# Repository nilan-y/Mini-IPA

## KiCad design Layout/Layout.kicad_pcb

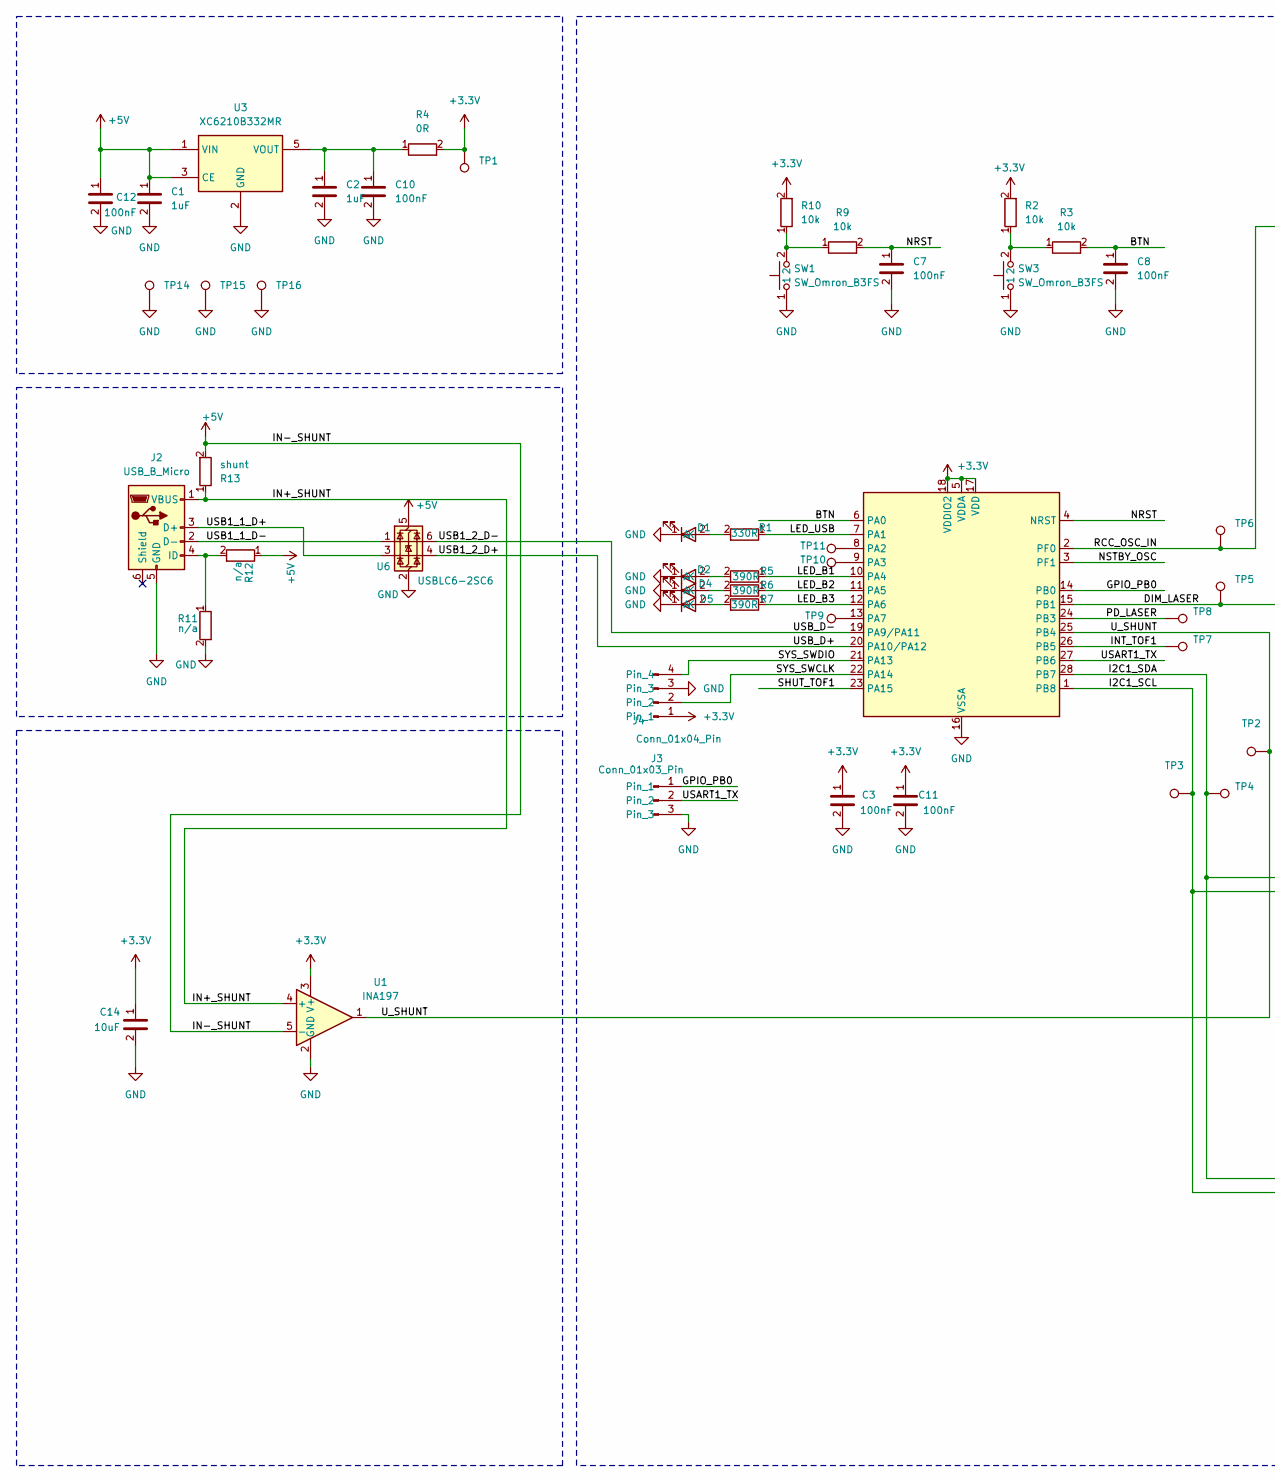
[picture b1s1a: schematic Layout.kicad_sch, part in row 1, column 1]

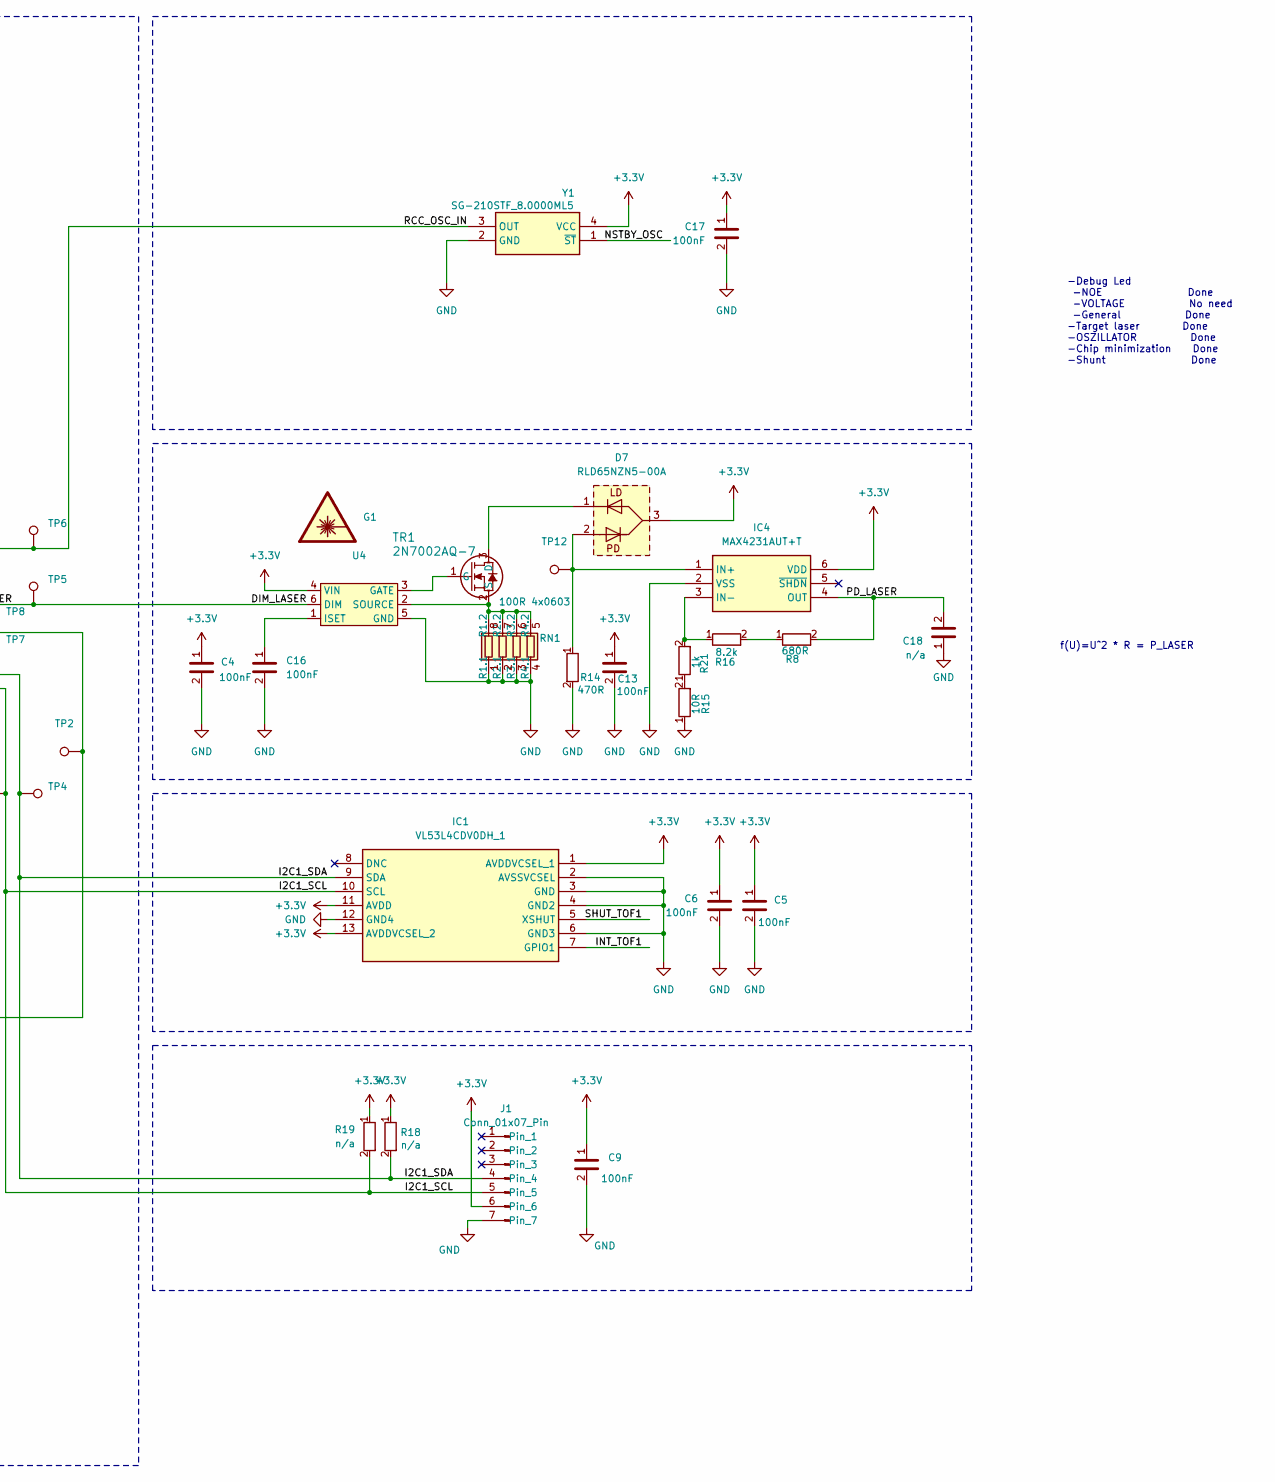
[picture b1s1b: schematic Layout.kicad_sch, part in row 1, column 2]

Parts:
C1, C2: 1uF; C_0402_1005Metric
C3, C4, C5, C6, C7, C8, C9, C10, C11, C12, C13, C16, C17: 100nF; C_0402_1005Metric
C14: 10uF; C_0402_1005Metric
C18: n/a; C_0402_1005Metric
D1: YELLOW LED; LED_0603_1608Metric
D2, D4, D5: BLUE LED; LED_0603_1608Metric
D7: RLD65NZN5-00A; RLD65NZN500A; Mouser Part Number 755-RLD65NZN5-00A
G1: Laser_Warnschild
IC1: VL53L4CDV0DH_1; VL53L4CDV0DH1; Mouser Part Number 511-VL53L4CDV0DH/1
IC3: STM32F042G4U6; uC_Footprint; Mouser Part Number 511-STM32F042G4U6
IC4: MAX4231AUT+T; SOT-23-6; Mouser Part Number 700-MAX4231AUTT
J1: Conn_01x07_Pin; PinHeader_1x07_P2.54mm_Vertical_SMD_Pin1Left
J2: USB_B_Micro; USB_Micro-B_Amphenol_10118193-0001LF_Horizontal
J3: Conn_01x03_Pin; PinHeader_1x03_P2.54mm_Vertical
J4: Conn_01x04_Pin; PinHeader_1x04_P2.54mm_Vertical
R1: 330R; R_0402_1005Metric
R2, R3, R9, R10: 10k; R_0402_1005Metric
R4: 0R; R_0603_1608Metric
R5, R6, R7: 390R; R_0402_1005Metric
R8: 680R; R_0402_1005Metric
R11, R12, R18, R19: n/a; R_0402_1005Metric
R13: shunt; R_2512_6332Metric
R14: 470R; R_0402_1005Metric
R15: 10R; R_0402_1005Metric
R16: 8.2k; R_0402_1005Metric
R21: 1k; R_0402_1005Metric
RN1: 100R 4x0603; R_Array_Concave_4x0603
SW1, SW3: SW_Omron_B3FS; SW_SPST_B3S-1000
TP1, TP2, TP3, TP4, TP5, TP6, TP7, TP8, TP12, TP14, TP15, TP16: Testpoint; TestPoint_Pad_D1.0mm
TP9, TP10, TP11: TestPoint; TestPoint_Pad_2.5x2.5mm
TR1: 2N7002AQ-7; SOT-23-3
U1: INA197; SOT-23-5
U3: XC6210B332MR; SOT-23-5
U4: SOT-23-6
U6: USBLC6-2SC6; SOT-23-6
Y1: SG-210STF_8.0000ML5; SG210STF480000ML5; Mouser Part Number 732-SG-210STF48.0ML5

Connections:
+3.3V: C3.1, C4.1, C5.1, C6.1, C9.1, C11.1, C13.1, C14.1, C17.1, D7.3, IC1.1 (AVDDVCSEL_1), IC1.11 (AVDD), IC1.13 (AVDDVCSEL_2), IC3.5 (VDDA), IC3.17 (VDD), IC3.18 (VDDIO2), IC4.6 (VDD), J1.6, J4.1, R2.2, R4.2, R10.2, R18.1, R19.1, TP1.1, U1.3 (V+), U4.4 (VIN), Y1.4 (VCC)
+5V: C1.1, C12.1, R12.1, R13.2, U1.5 (-), U3.1 (VIN), U3.3 (CE), U6.5 (VBUS)
/BTN: C8.1, IC3.6 (PA0), R3.2
/DIM_LASER: IC3.15 (PB1), TP5.1, U4.6 (DIM)
/GPIO_PB0: IC3.14 (PB0), J3.1
/I2C1_SCL: IC1.10 (SCL), IC3.1 (PB8), J1.5, R19.2, TP3.1
/I2C1_SDA: IC1.9 (SDA), IC3.28 (PB7), J1.4, R18.2, TP4.1
/IN+_SHUNT: J2.1 (VBUS), R13.1, U1.4 (+)
/INT_TOF1: IC1.7 (GPIO1), IC3.26 (PB5), TP7.1
/LED_B1: IC3.10 (PA4), R5.1
/LED_B2: IC3.11 (PA5), R6.1
/LED_B3: IC3.12 (PA6), R7.1
/LED_USB: IC3.7 (PA1), R1.1
/NRST: C7.1, IC3.4 (NRST), R9.2
/NSTBY_OSC: IC3.3 (PF1), Y1.1 (~ST)
/PD_LASER: C18.2, IC3.24 (PB3), IC4.4 (OUT), R8.2, TP8.1
/RCC_OSC_IN: IC3.2 (PF0), TP6.1, Y1.3 (OUT)
/SHUT_TOF1: IC1.5 (XSHUT), IC3.23 (PA15)
/SYS_SWCLK: IC3.22 (PA14), J4.2
/SYS_SWDIO: IC3.21 (PA13), J4.4
/USART1_TX: IC3.27 (PB6), J3.2
/USB1_1_D+: J2.3 (D+), U6.3 (I/O2)
/USB1_1_D-: J2.2 (D-), U6.1 (I/O1)
/USB1_2_D+: IC3.20 (PA10/PA12), U6.4 (I/O2)
/USB1_2_D-: IC3.19 (PA9/PA11), U6.6 (I/O1)
/U_SHUNT: IC3.25 (PB4), TP2.1, U1.1
GND: C1.2, C2.2, C3.2, C4.2, C5.2, C6.2, C7.2, C8.2, C9.2, C10.2, C11.2, C12.2, C13.2, C14.2, C16.2, C17.2, C18.1, D1.1 (K), D2.1 (K), D4.1 (K), D5.1 (K), IC1.2 (AVSSVCSEL), IC1.3 (GND), IC1.4 (GND2), IC1.6 (GND3), IC1.12 (GND4), IC3.16 (VSSA), IC4.2 (VSS), J1.7, J2.5 (GND), J3.3, J4.3, R11.2, R14.2, R15.1, RN1.1 (R1.1), RN1.2 (R2.1), RN1.3 (R3.1), RN1.4 (R4.1), SW1.1, SW3.1, TP14.1, TP15.1, TP16.1, U1.2 (GND), U3.2 (GND), U4.5 (GND), U6.2 (GND), Y1.2 (GND)
unnamed: D1.2 (A), R1.2
unnamed: D2.2 (A), R5.2
unnamed: D4.2 (A), R6.2
unnamed: D5.2 (A), R7.2
unnamed: IC3.8 (PA2), TP11.1
unnamed: IC3.9 (PA3), TP10.1
unnamed: IC3.13 (PA7), TP9.1
unnamed: D7.2, IC4.1 (IN+), R14.1, TP12.1
unnamed: IC4.3 (IN-), R16.1, R21.2
unnamed: J2.4 (ID), R11.1, R12.2
unnamed: R2.1, R3.1, SW3.2
unnamed: R9.1, R10.1, SW1.2
unnamed: R15.2, R21.1
unnamed: R8.1, R16.2
unnamed: RN1.5 (R4.2), RN1.6 (R3.2), RN1.7 (R2.2), RN1.8 (R1.2), TR1.2 (S), U4.2 (SOURCE)
unnamed: D7.1, TR1.3 (D)
unnamed: TR1.1 (G), U4.3 (GATE)
unnamed: C2.1, C10.1, R4.1, U3.5 (VOUT)
unnamed: C16.1, U4.1 (ISET)

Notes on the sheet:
f(U)=U^2 * R = P_LASER
-Debug Led -NOE Done -VOLTAGE No need -General Done -Target laser Done -OSZILLATOR Done -Chip minimization Done -Shunt Done

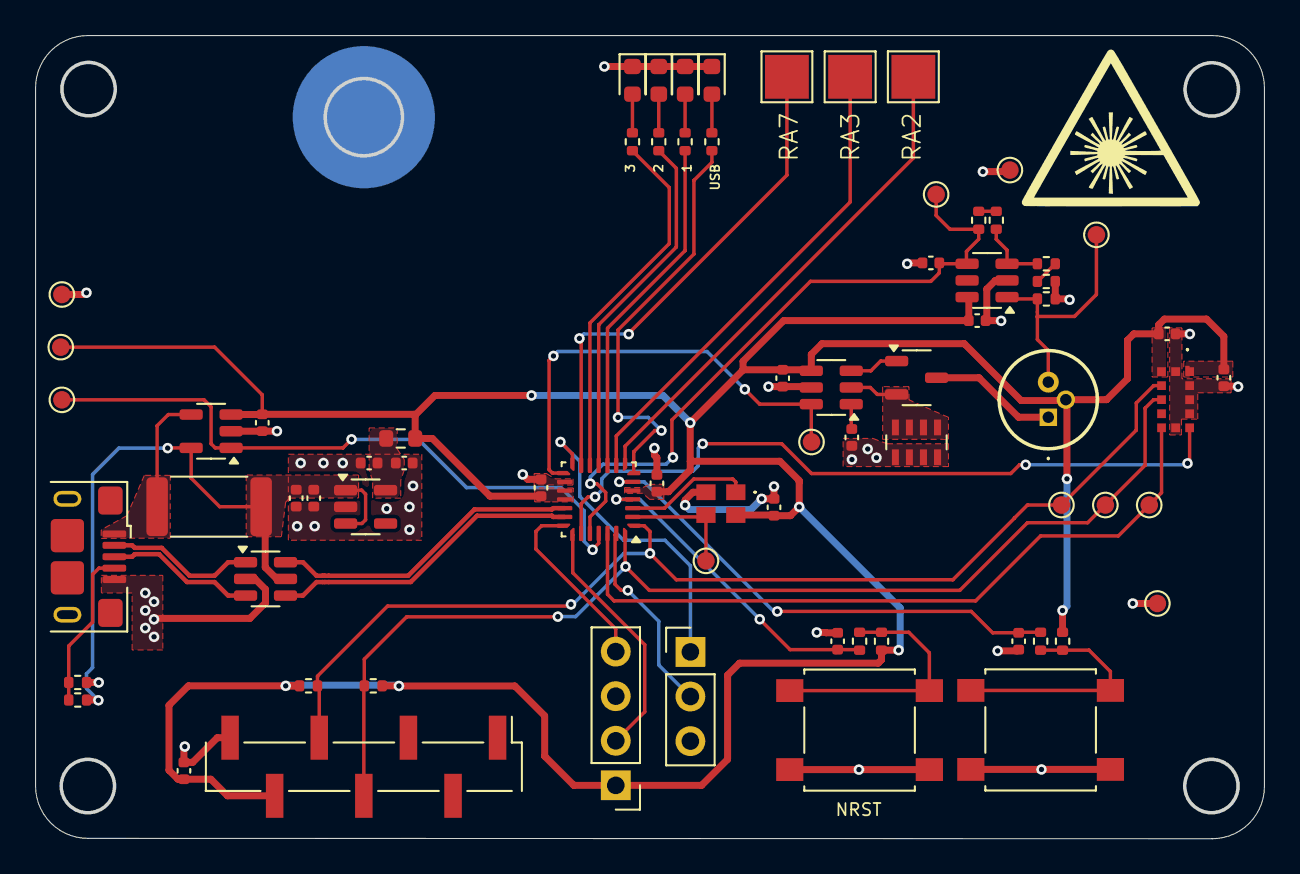
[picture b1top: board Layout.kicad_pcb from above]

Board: 2 copper layers, 70.0 x 45.7 mm, 73 parts (0 on the bottom side), 46 nets.

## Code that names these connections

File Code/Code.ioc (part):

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Mcu.Name=STM32F042G(4-6)Ux
Mcu.Package=UFQFPN28
Mcu.UserName=STM32F042G6Ux
PA0.GPIOParameters=GPIO_Label
PA0.GPIO_Label=BTN
PA0.Signal=GPIO_Input
PA1.GPIOParameters=GPIO_Label
PA1.GPIO_Label=LED_USB
PA1.Signal=GPIO_Output
PA11.Mode=Device
PA11.Signal=USB_DM
PA12.Mode=Device
PA12.Signal=USB_DP
PA13.Mode=Serial_Wire
PA13.Signal=SYS_SWDIO
PA14.Mode=Serial_Wire
PA14.Signal=SYS_SWCLK
PA15.GPIOParameters=GPIO_Label
PA15.GPIO_Label=SHUT_TOF
PA15.Signal=GPIO_Output
PA2.GPIOParameters=GPIO_Label
PA2.GPIO_Label=PD_LASER
PA2.Mode=IN2
PA2.Signal=ADC_IN2
PA3.GPIOParameters=GPIO_Label
PA3.GPIO_Label=U_SHUNT
PA3.Mode=IN3
PA3.Signal=ADC_IN3
PA4.GPIOParameters=GPIO_Label
PA4.GPIO_Label=LED_B1
PA4.Signal=GPIO_Output
PA5.GPIOParameters=GPIO_Label
PA5.GPIO_Label=LED_B2
PA5.Signal=GPIO_Output
PA6.GPIOParameters=GPIO_Label
PA6.GPIO_Label=LED_B3
PA6.Signal=GPIO_Output
PB0.Signal=GPIO_Output
PB1.Mode=PWM Generation3 CH3N
PB1.Signal=TIM1_CH3N
PB5.GPIOParameters=GPIO_Label
PB5.GPIO_Label=INT_TOF
PB5.Signal=GPXTI5
PB7.Mode=I2C
PB7.Signal=I2C1_SDA
PB8.Mode=I2C
PB8.Signal=I2C1_SCL
PF0-OSC_IN.Mode=HSE-External-Clock-Source
PF0-OSC_IN.Signal=RCC_OSC_IN
PF1-OSC_OUT.GPIOParameters=GPIO_Label
PF1-OSC_OUT.GPIO_Label=NSTBY_OSC
PF1-OSC_OUT.Signal=GPIO_Output
RCC.SYSCLKFreq_VALUE=48000000
RCC.SYSCLKSource=RCC_SYSCLKSOURCE_HSI48
board=custom
